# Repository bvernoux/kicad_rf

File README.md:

# kicad_rf
KiCad RF experimentations with some RF boards including Qucs Projects and Measurements with VNA HP8753D(30KHz-6GHz)

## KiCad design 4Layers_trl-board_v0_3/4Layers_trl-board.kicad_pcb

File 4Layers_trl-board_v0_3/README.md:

4Layers_trl-board_v0_3
==============================

This board is based on Mario Hellmich's design see https://www.mariohellmich.de/projects/trl-cal/trl-cal.html

TRL Calibration Board for evaluation of Southwest Microwave 1092-02A-5(up to 40 GHz) or BELFUSE / Cinch 142-0771-831(Up to 26.5GHz) or cheap SMA connectors.
50 Ohms Impedanced Matched with OSHPark 4Layers FR408-HR or JLCPCB 4Layers JLC7628

It contains following features:
* A thru standard for TRL
* A 50 Ohms match standard
* A 25 Ohms mismatch standard for verification
* An open standard for verification
* A short standard, used as a reflect standard for TRL
* A line of 45 mm length (Called also "Line 76mm" to reflect total length), used as a line standard for TRL
* A series fixture for 0402 components
* A shunt fixture for 0402 components

The board is designed assuming the following parameters (based on [OSH Park 4 Layers 190Tg FR408-HR specifications](https://docs.oshpark.com/services/four-layer)):
* Base Material / Board thickness: 1.6 mm (63 mil)
* Conductor Height 0.20mm (or 0.17mm FR408-HR)
* Center Conductor Width: 0.36 mm (14.17 mil)
* Gap Width: 0.25 mm (9.84 mil)
* Permittivity: FR408-HR 3.66 (3.68 @2GHz) or FR4 4.6
* Loss Tangent: 0.0092 @2GHz
* Copper Weight: 1oz outer (35µm), 1/2oz inner (17.5µm)
* Trace surface: Cu
* Impedance: 50 Ohms (+/-2 Ohms)
* PCB Finish: ENIG (Gold)

For more details on TRL see https://www.mariohellmich.de/projects/trl-cal/trl-cal.html

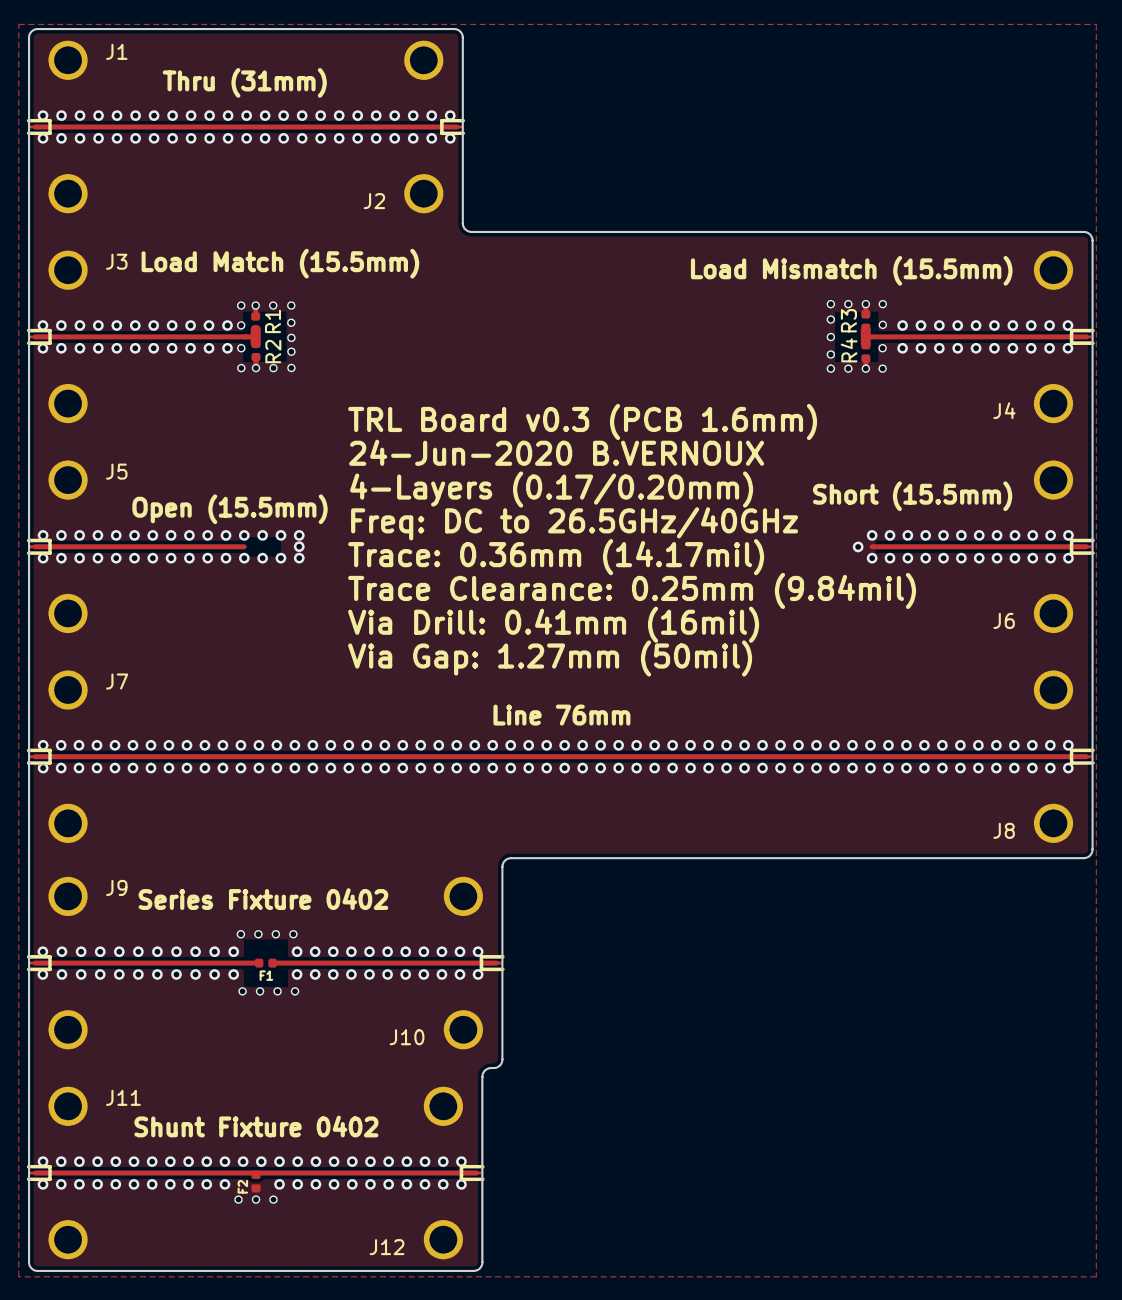
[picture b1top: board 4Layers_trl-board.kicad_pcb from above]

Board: 4 copper layers, 76.0 x 88.8 mm, 18 parts (0 on the bottom side), 8 nets.

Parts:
F1, F2: Fixture 0402; C_0402_1005Metric
J1, J2, J3, J4, J5, J6, J7, J8, J9, J10, J11, J12: 142-0771-831; Southwest_Microwave_1092-02A-5
R1, R2: 100; R_0402_1005Metric
R3, R4: 50; R_0402_1005Metric

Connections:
GND: F2.1, J1.2, J2.2, J3.2, J4.2, J5.2, J6.1, J6.2, J7.2, J8.2, J9.2, J10.2, J11.2, J12.2, R1.2, R2.2, R3.2, R4.2
unnamed: F1.1, J10.1
unnamed: F1.2, J9.1
unnamed: F2.2, J11.1, J12.1
unnamed: J1.1, J2.1
unnamed: J3.1, R1.1, R2.1
unnamed: J4.1, R3.1, R4.1
unnamed: J7.1, J8.1

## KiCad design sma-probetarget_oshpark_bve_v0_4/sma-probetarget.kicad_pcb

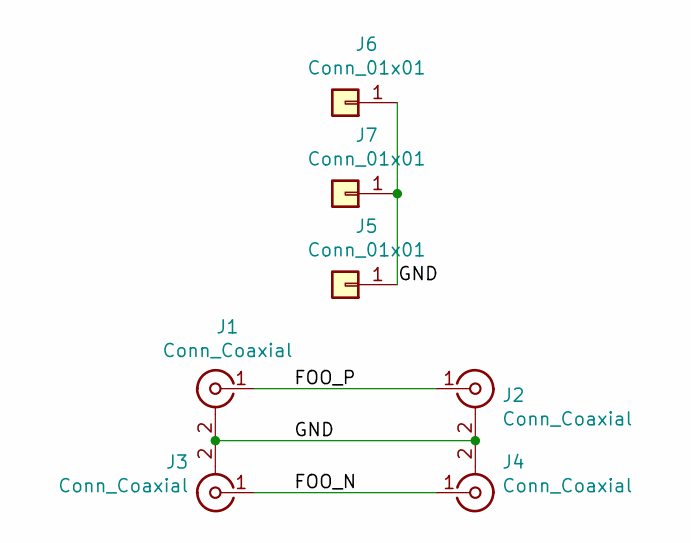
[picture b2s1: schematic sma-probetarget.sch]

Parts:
J1, J2, J3, J4: Conn_Coaxial; SMA-Launcher_Cinch_142-0771-831
J5: Conn_01x01; TESTPOINT_SMT_KEYSTONE_5016
J6, J7: Conn_01x01; TESTPOINT_BARETRACE_328UM

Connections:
/FOO_N: J3.1 (In), J4.1 (In)
/FOO_P: J1.1 (In), J2.1 (In)
/GND: J1.2 (Ext), J2.2 (Ext), J3.2 (Ext), J4.2 (Ext), J5.1, J6.1, J7.1

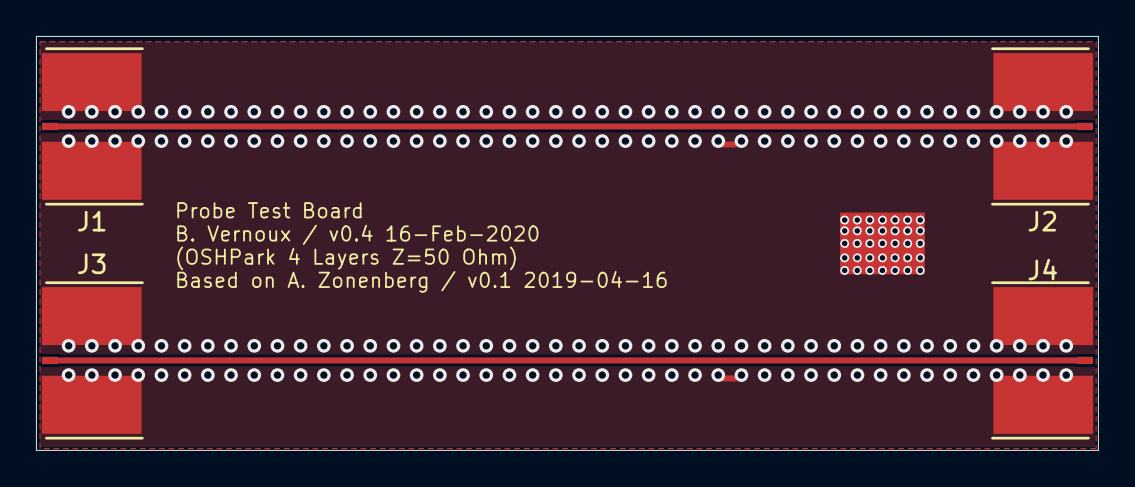
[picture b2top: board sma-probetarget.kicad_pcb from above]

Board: 4 copper layers, 59.0 x 23.0 mm, 7 parts (0 on the bottom side), 3 nets.

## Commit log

2020-02-17 Import OSHPark_4Layers_trl-board_v0_1
2020-02-17 Add README.md + Pictures
2020-05-07 sma-probetarget_oshpark_bve_v0_4 first import
2020-06-24 4Layers trl-board v0.3
2021-06-12 Footprint for SMA Edge connector (up to 40GHz) to "rule them all" Southwest Microwave 1092-02A-5 Amphenol RF 901_10510-2 & 901-10511-3 Compatible with Belfuse 142-0771-831 and Mueller Electric Co BU-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
2021-06-12 Changed holes size from 0.95mm to 1.1mm (recommendations confirmed by Technical support of Amphenol RF) for the 4 "legs" for part 901-10510-2
2021-07-25 First import 6 Layers trl-board microstrip v0.1 OSHPark
2021-07-25 Changed holes size from 1.1mm to 1.0mm (as 1.1mm is a bit loose) for the 4 "legs" for part 901-10510-2
2021-08-17 Updated footprint for easier soldering
2021-08-17 Added footprint for basic components R/L/C/DIODE/LED
